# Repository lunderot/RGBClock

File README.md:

A clock with wifi connectivity and a RGB display.  

The clock uses an esp8266 as the main processor with ws2812 LEDs for the display.  
The front face is 3d printed in PLA.

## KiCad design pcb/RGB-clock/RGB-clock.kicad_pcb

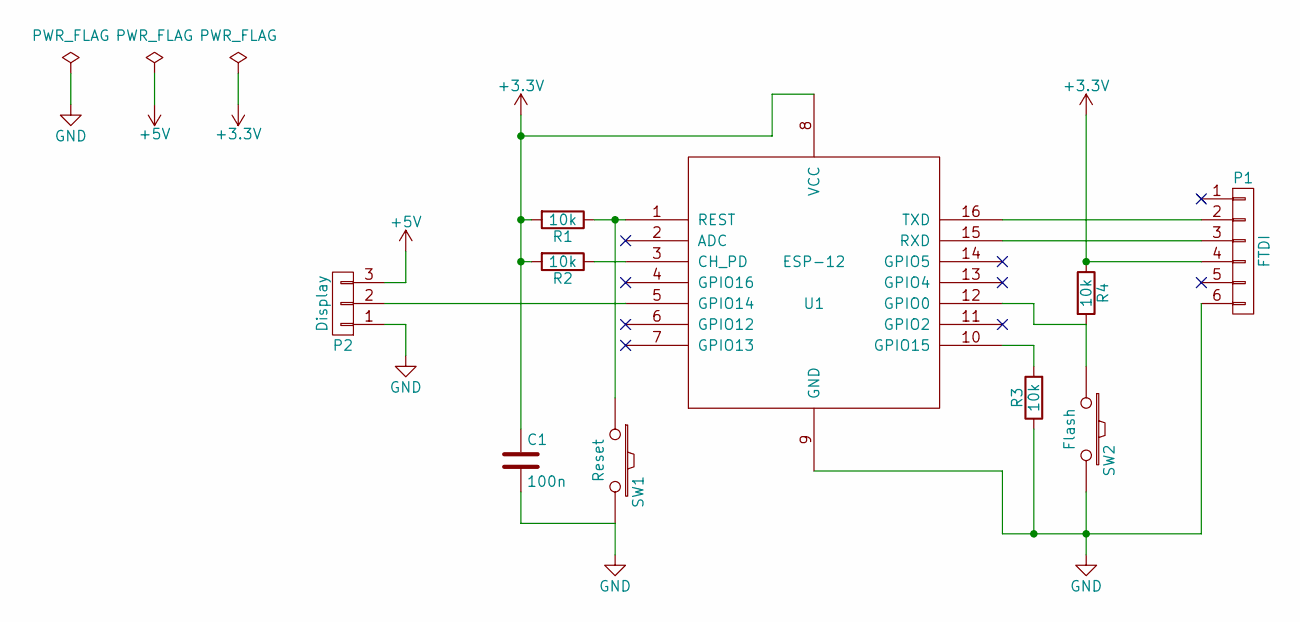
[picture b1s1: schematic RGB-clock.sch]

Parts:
C1: 100n; C_0805_HandSoldering
P1: FTDI; Pin_Header_Straight_1x06_Pitch2.54mm
P2: Display; Pin_Header_Straight_1x03_Pitch2.54mm
R1, R2, R3, R4: 10k; R_0805_HandSoldering
SW1: Reset; SW_SPST_REED_CT05-XXXX-G1
SW2: Flash; SW_SPST_REED_CT05-XXXX-G1
U1: ESP-12

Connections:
+3V3: C1.1, P1.4, R1.2, R2.2, R4.1, U1.8 (VCC)
+5V: P2.3
GND: C1.2, P1.6, P2.1, R3.1, SW1.2, SW2.2, U1.9 (GND)
unnamed: P1.2, U1.16 (TXD)
unnamed: P1.3, U1.15 (RXD)
unnamed: P2.2, U1.5 (GPIO14)
unnamed: R1.1, SW1.1, U1.1 (REST)
unnamed: R2.1, U1.3 (CH_PD)
unnamed: R3.2, U1.10 (GPIO15)
unnamed: R4.2, SW2.1, U1.12 (GPIO0)

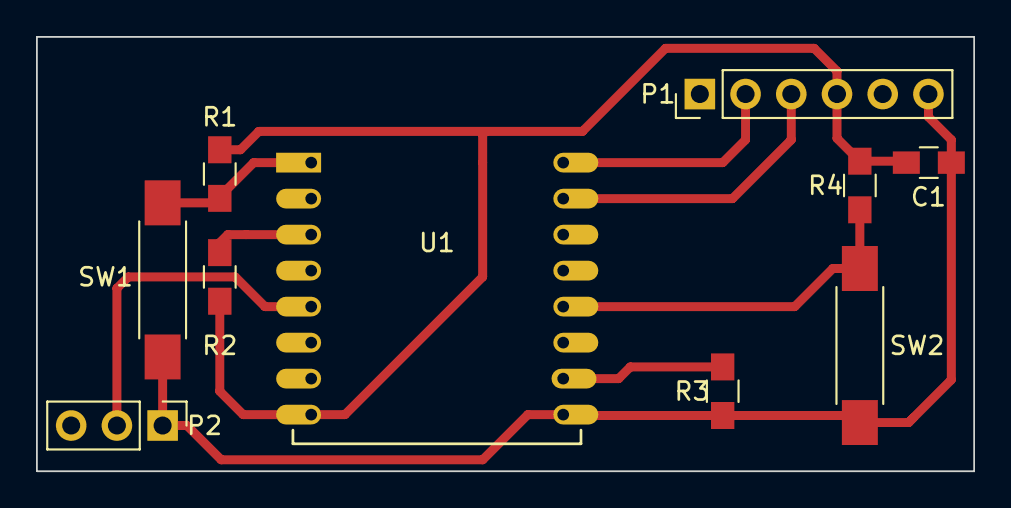
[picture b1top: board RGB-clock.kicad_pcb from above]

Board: 2 copper layers, 52.1 x 24.1 mm, 10 parts (0 on the bottom side), 9 nets.

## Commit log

2018-06-02 Initial commit
    Added CAD files
    Added basic esp program with a HTTP request
2018-06-02 Now works with HTTPS and gets the redirect URL from google script
2018-06-02 Now connects to the redirected URL
2018-06-02 Program is now using function callbacks to process HTTP data
2018-06-06 Now the program stores the current time and can display numbers
2018-06-12 Time is now displayed
2018-07-08 Changed displayNumber
2018-08-13 Added USB connector model
2018-08-15 Added PCB design
2018-12-21 Reamade model in pure OpenSCAD
2018-12-24 Timezone is now set in the google script
2018-12-29 Cleaned up code
2019-01-26 Added google script
2019-03-31 Added update time function
2019-07-20 Updated PCB
2019-11-01 Code cleanup
2020-04-21 Added readme
